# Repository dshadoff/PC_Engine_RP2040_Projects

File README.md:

# PC_Engine_RP2040_Projects - Projects designed for PC Engine, using RPi Pico or other RP2040 hardware

## [Memory Base 128 reimplementation](https://github.com/dshadoff/PC_Engine_RP2040_Projects/tree/main/Membase)

This is the third implementation of the Memory Base 128 I have written for modern hardware, and the easiest code to read.
The PIOs areused for edge-sensing of the data input, and the ARM core is used for processing.

The data is loaded into SRAM at startup, and saved into Flash after transactions take place.  This may not be ideal, as the
device is not capable of processing additional commands while the Flash flush is in progress (it takes place 0.75 seconds
after the last read/write of a group of read or write transactions).

## [PC Engine USB Mouse adapter](https://github.com/dshadoff/PC_Engine_RP2040_Projects/tree/main/PCEMouse)

This allows a modern USB mouse to be used by a PC Engine machine.  The PC Engine did have a mouse later in the console's
lifetime; it was a mouse with a rotating ball and a cord (anybody familiar with this type of mouse would be familiar
with the desire to use a modern cordless optical mouse).

The RP2040 board is used as the USB Host for the mouse, and PIOs are used for signalling to the PC Engine console.

## Others

Other Projects are coming... the PIOs on the RPi Pico are very interesting and flexible, so will be well-suited to
retrocomputing/retrogaming projects.

## Notes
I initially used the Adafruit QtPy RP2040 as much as possible, as it is a compact form factor which is easy to design around; however,
I have also warmed up to the Seeed XIAO for having the same form factor, but with no parts on the underside (making soldering on the
castellations easier), and lower price.  The Adafruit KB2040 is also very attractive because it breaks out the USB pins so that alternate
USB connectors can be used (such as USB-A connectors for mouse devices).

Unfortunately, for the QtPy 2040, the Adafruit site tries to direct all users toward CircuitPython rather than C/C++ (the Pi SDK), and
as a result, Pinout pages of the "Pinout" page for their RP2040 devices don't include references to the GPIO numbers.

Therefore, I am including a graphic here:

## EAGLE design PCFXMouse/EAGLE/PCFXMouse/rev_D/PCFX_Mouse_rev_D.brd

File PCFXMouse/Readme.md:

# PC_Engine_RP2040_Projects - PC-FX Mouse converter

## Overview

This project is intended to allow use of a standard USB mouse on a PC-FX.
I have revised this project a few times, and arrived at using an Adafruit KB2040 microcontroller board, as it uses the
excellent RP2040 microcontroller, and due to its breakout of the USB lines, which allows for an external USB-A connector.

## PC Board and Assembly

I designed all boards using the free version of EAGLE (2-layer, less than 100mm on both X- and Y- axes).
The gerbers are included in this repository, in case you want to get your own set made.

I have included the gerbers and relevant bom.csv and assembly.csv files to get these boards
assembled by JLCPCB, but you will still need the following parts:
- (1) Adafruit KB2040 RP2040 microcontroller board
- (7) pieces of Mill-Max pin&socket connector, Part number 4401-0-15-80-18-27-04-0

Optional:
- (2) 13-pin headers.  You may also want to use female pin header sockets in case you need to remove the microcontroller board.
I recommend using short/low-profile header sockets in this case.

There are two PC Boards in this assembly; one functions as part of the host connector.
For that PC Board, you will need the Mill-Max pin&socket connectors.

The way I assembled it was to carefully put the pin connectors on their respective pins, then
position the PC board over top, and solder in place.

Steps to assembly:

See the Assembly Guide
**[See the Assembly Guide](Assembly.md)**

## Source Code

### Compilation

This code is now updated to Pico-SDK version 1.5.0, and should be built using that version of the SDK.
pico_sdk_import.cmake is from the SDK, but is required by CMake (and thus replicated here).

This is based on the TinyUSB Host HID example, and since this often changes (required by refactoring of
the Host HID code), the initial commit baseline is the source ocde of that example.

To build the source, first ensure that you have the right version of the RaspberryPi/piso-sdk installed.
As this board targets the Adafruit KB2040 board, you should run the build_kb2040.sh script (under UNIX).
Then, "cd build" and "make".

I have also included a release version of the program as a uf2 file in the releases/ folder; just drag and drop it
onto the virtual drive presented when putting the board into BOOTSEL mode (holding the 'boot' button, connect the
board by USB to a host computer, and release the button; a new drive should appear on the computer).

### Theory of Operation

At a high level, this is a multi-processor system, withe the division of work as follows:
- CPU0 : perform USB scanning, accumulate X/Y offsets and button status, and push a word conatining all this to PIO State Machine #1.
At intervals, detect whether the scan interval must be complete (after a certain threshold period).
- CPU1 : watch PIO State Machine #1 for the signal identifying start of scan; set locking to prevent mid-scan updates
- PIO State Machine #1 : Monitor host electrical signals, and send the appropriate bit(s) back to host according to protocol
- PIO State Machine #2 : Watch the trigger line identifying the start of scan, and send the signal back to CPU1

#### PC-FX Mouse/Controller Protocol:

Similar to the NES or SNES, the PC-FX Engine triggers a start-of-read trigger by bringing the LATCH line
low.  The first bit of data is output at this time. After the LATCH signal returns to the high state, each
subsequent bit is sent at the transition of the CLOCK signal to high.

In the below diagram, LATCH is the top trace, CLOCK is the middle trace, and DATA sent back is the bottom trace
(/OE defines the data direction - LOW=Read controller; HIGH=Write to controller:\

The first bit sent is the least significant, and the most significant bit is sent last.  The last byte in
the sequence is a controller type identifier - 0x2F = Mouse, and 0x0F = Joypad.

The below data diagram shows how the data is internally passed to the state machien for output:

    Structure of the word sent to the FIFO from the ARM:
    |00101111|111111bb|xxxxxxxx|yyyyyyyy| (PCFX mouse)
    |00001111|11111111|1m1mdddd|rsbbbbbb| (PCFX joypad)
    
     Where:
      0 = must be zero
      1 = must be one
     MOUSE:
      b = button values, arranged in right/left sequence for PC-FX use
      x = mouse 'x' movement; right is {1 - 0x7F} ; left is {0xFF - 0x80 } -> but send as 1's complement !
      y = mouse 'y' movement; down  is {1 - 0x7F} ;  up  is {0xFF - 0x80 } -> but send as 1's complement !
    
     NOTES:
      - PC-FX left/right is (-/+) (but sent as complement - i.e. sned 0xFF if value is zero)
      - PC-FX up/down is (-/+) (but sent as complement - i.e. sned 0xFF if value is zero)

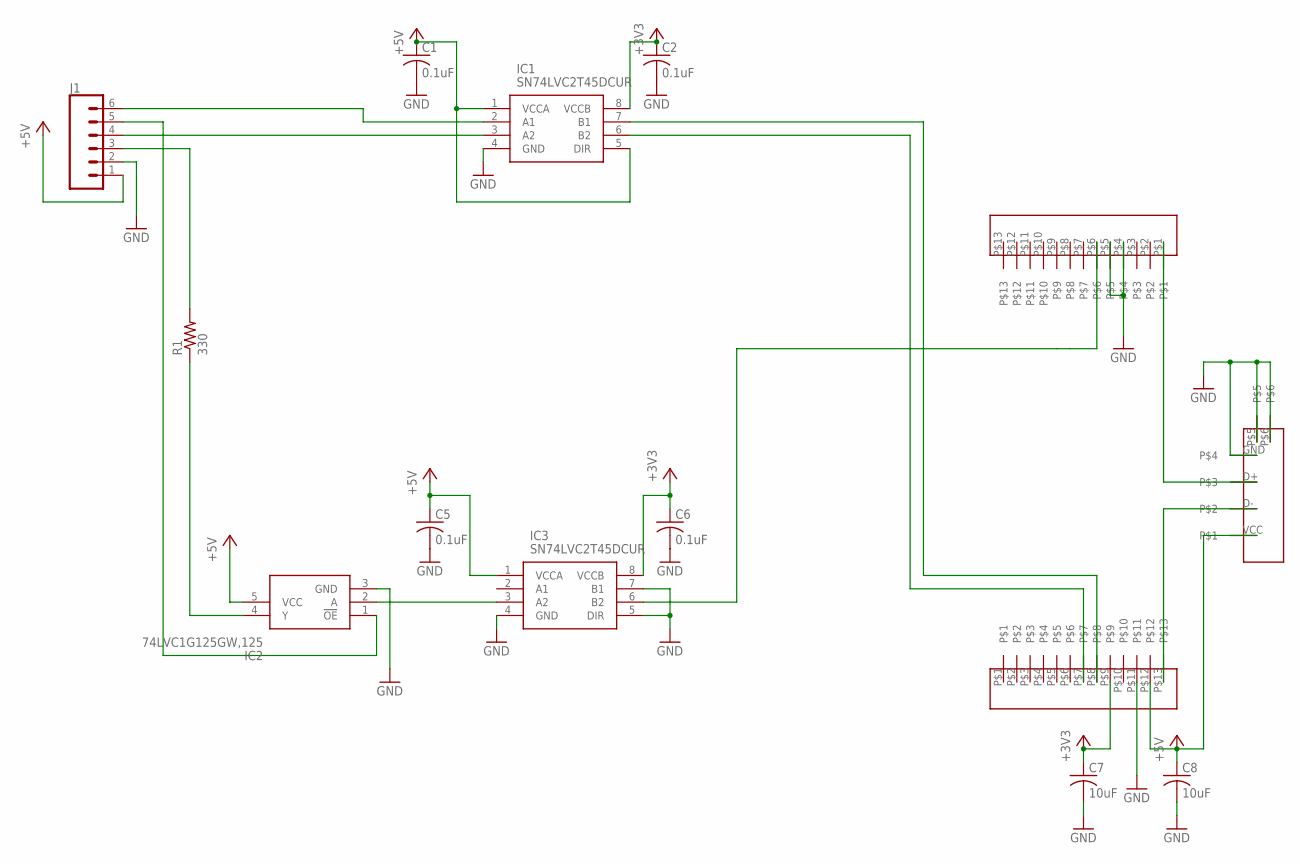
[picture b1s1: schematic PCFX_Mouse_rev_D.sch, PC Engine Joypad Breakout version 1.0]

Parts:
C1, C2, C5, C6: 0.1uF; C0402
C7, C8: 10uF; C0805
IC1, IC3: SN74LVC2T45DCUR; SOP50P310X90-8N
IC2: 74LVC1G125GW,125; SOT65P212X110-5N
J1: CONN_06NO_SILK_FEMALE_PTH; 1X06_NO_SILK
J2, J3: CONN_1X13
R1: 330; R0402
U$1: 912-121A2026S10100

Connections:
+3V3: C2.1, C6.1, C7.1, IC1.8 (VCCB), IC3.8 (VCCB), J2.P$9
+5V: C1.1, C5.1, C8.1, IC1.1 (VCCA), IC1.5 (DIR), IC2.5 (VCC), IC3.1 (VCCA), J1.1, J2.P$12, U$1.VCC
CLK: IC1.3 (A2), J1.4
DATA: J1.3, R1.2
GND: C1.2, C2.2, C5.2, C6.2, C7.2, C8.2, IC1.4 (GND), IC2.3 (GND), IC3.4 (GND), IC3.5 (DIR), IC3.7 (B1), J1.2, J2.P$11, J3.P$4, J3.P$5, U$1.GND, U$1.P$5, U$1.P$6
LATCH: IC1.2 (A1), J1.6
unnamed: IC2.2 (A), IC3.3 (A2)
unnamed: IC1.7 (B1), J2.P$8
unnamed: IC3.6 (B2), J3.P$6
unnamed: J2.P$13, U$1.D-
unnamed: IC2.1 (!OE), J1.5
unnamed: J3.P$1, U$1.D+
unnamed: IC1.6 (B2), J2.P$7
unnamed: IC2.4 (Y), R1.1

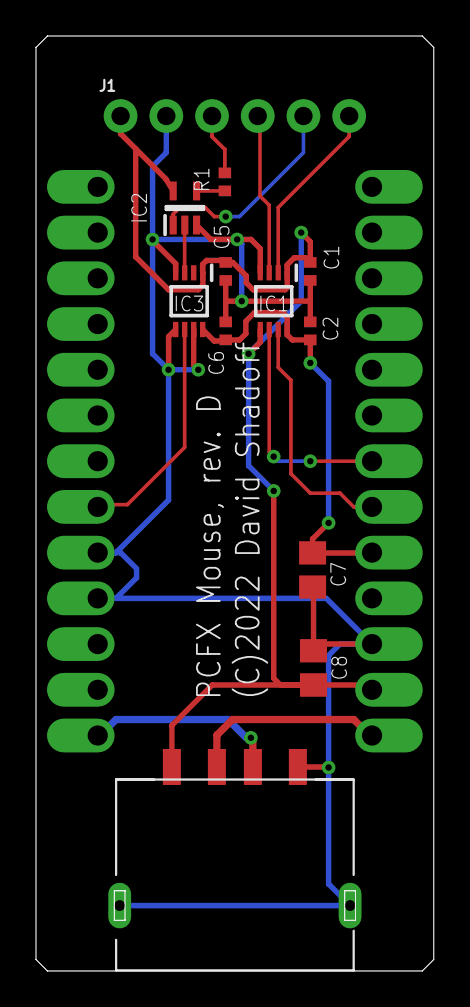
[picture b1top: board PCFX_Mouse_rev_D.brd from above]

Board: 2 copper layers, 22.1 x 51.9 mm, 14 parts (0 on the bottom side), 14 nets.

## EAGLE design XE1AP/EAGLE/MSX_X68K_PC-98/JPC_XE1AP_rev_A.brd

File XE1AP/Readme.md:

# PC_Engine_RP2040_Projects - XE-1AP Analog Joystick Converter

## Overview

This project is intended to allow use of a standard USB-based PS4 gamepad on a PC Engine as a XE-1AP analog joypad.
While the code and board are in working condition, there is likely still room for improvement, as I feel that
analog positioning may not be as smooth as it could be.

## PC Board and Assembly

This project has several different possible "carrier" boards, depending on which host machine you are targeting.
All are deigned in EAGLE; all include schematic, board layout, and gerber files.  They also include BOM and assembly files
for JLCPCB SMD assembly.

### PC Engine

This is the same PC Board used in the "PCEMouse" project in this repository (KB2040 board version), however I have copied
the contents here for simplicity for users.

### Japanese PCs (MSX, X68000, PC-98, etc.)

This is a slightly differnet carrier board with a DB-9 connector, for Japanese MSX, X68000, and PC-98 machines.  It uses the SAME
KB2040 and the SAME firmware as the PC Engine version.

Next, I intend to make a board to work with the Megadrive.

## Source Code

### Compilation

This was updated to use Pico-SDK version 1.5.0 .

pico_sdk_import.cmake is from the SDK, but is required by CMake (and thus replicated here)

This is based on the TinyUSB Host HID controller example, and since this often changes (required by refactoring of
the Host HID code), the initial commit baseline is the source code of that example.

To build the source, first ensure that you have the right version of the RaspberryPi/piso-sdk installed.
As this board targets the Adafruit KB2040 board, you should run the build_ada_kb2040.sh script (under UNIX).
Then, "cd build" and "make".

I have also included a release version of the program as a uf2 file in the releases/ folder; just drag and drop it
onto the virtual drive presented when putting the board into BOOTSEL mode (holding the 'boot' button, connect the
board by USB to a host computer, and release the button; a new drive should appear on the computer).

### Theory of Operation

At a high level, this is a multi-processor system, withe the division of work as follows:
- CPU0 : perform USB scanning, analyze controller button statuses and joysticks' X/Y offsets, and keep the data up-to-date in a temporary storage area.
- CPU1 : watch PIO State Machine #1 for the signal identifying start of scan, set locking to prevent mid-scan updates, and push the series of last-known-good data to state machine #2.
- PIO State Machine #1 : Monitor host electrical signals, blocking thread #1 until triggereed, and signalling state machine #2 to start its
protocol via an IRQ signal.
- PIO State Machine #2 : Wait for IRQ signal from state machine #1, and then send the data out on the GPIOs according to the standard timing (get the data from the TX FIFO as sent by CPU1).
- PIO State Machine #3 : Watch the SEL line identifying which bits to multiplex, and send the correct bits out through the data outputs
(note: the XE3-HE did not multiplex these in the same sequence as the Megadrive, so some bit-rearranging takes place here).

#### XE-1AP Protocol:

The PC Engine triggers a start-of-read trigger by flipping the CLR line low briefly, and returning it to HIGH.  Note that this is
not normal behaviour, and the XE-1AP is NOT compatible with the multi-tap. Immediately following the rise of the CLR line, the
joystick values are latched. During this time, SEL is held LOW as the PC Engine is expected to watch for state transitions on the
buttons 'I' and 'II', which are on D0 and D1 respectively.  D0 is LOW and D1 is HIGH during the waiting period.
After roughly 68.4 microseconds, data is ready, which is signalled by D1 (button 'II') transitioning low.

When the console sees this, its duty is to transition SEL to HIGH, in order to read the four data bits on D0-D3
(which normally correspond to UP/DOWN/LEFT/RIGHT), which in this situation correspond to the first nybble of data
from the joystick.  Then, SEL needs to transition back to LOW in order to monitor D0 and D1 again.  The window of data
availability (when button 'II' stays LOW) is fairly short, roughly 12.1 microseconds, requiring a tight loop on the
host console.

Before the next nybble is made available, button 'II' transitions HIGH for roughly 3.8 microseconds while data lines
transition.  Button 'I' transitions HIGH, representing the second nybble - and button 'II' transitions LOW again (for
12.1 microseconds again), signalling data ready, and the console needs to fetch the nybble by toggling SEL and reading
the lines during the availability window.

When button 'II' toggles high again, this time it stays high for longer (to prepare for the next 2 nybbles), at
21.8 microseconds.  The pattern repeats, with 6 bytes (12 nybbles) in all being transferred; the entire time from the
initial pulse to the end of the data transfer is roughly 350 microseconds.

Note that timing on this implementation is rounded to the next higher number of microseconds in most situations, with the difference
being removed from the 'dead' times between the second half of one byte, and the first half of the next byte being sent.

#### Data sequence output:

The sequence of data (and bit-order) is as follows (from original joystick):

All values are low when pressed, high when not pressed

 1. Buttons A, B, C, D - (Note: A is pressed if either A or A' is pressed; same with B or B')
 2. Buttons E1, E2, Start(F), Select (G)
 3. Top 4 bits of 'channel 0' (Y-axis;   limit up   = 0x00, limit down  = 0xFF)
 4. Top 4 bits of 'channel 1' (X-axis;   limit left = 0x00, limit right = 0xFF)
 5. Top 4 bits of 'channel 2' (Throttle; limit up   = 0xFF, limit down  = 0x00)
 6. 0000 (unused)
 7. Bottom 4 bits of 'channel 0' (Y-axis)
 8. Bottom 4 bits of 'channel 1' (X-axis)
 9. Bottom 4 bits of 'channel 2' (Throttle)
10. 0000 (unused)
11. Buttons A, B, A', B' (This can differentiate between the buttons, whereas scan #1 merges them)
12. 1111 (all high)

#### Logic state diagram:

**Compatibility:** Games which are not specifically written to support the X-HE3/XE-1AP in analog format will not work properly with this code.

Compatible games include:
 - AfterBurner II
 - Forgotten Worlds
 - Operation Wolf
 - Outrun

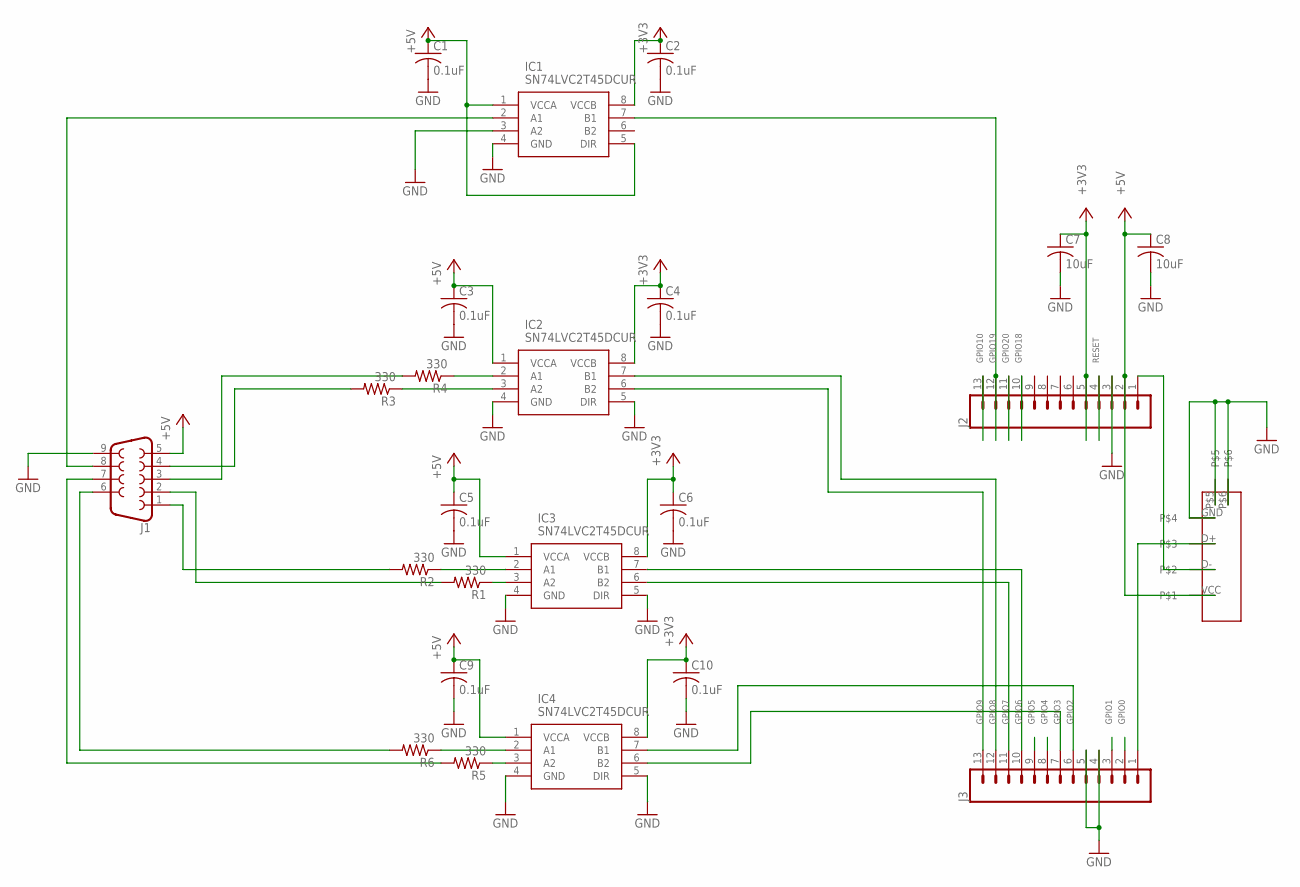
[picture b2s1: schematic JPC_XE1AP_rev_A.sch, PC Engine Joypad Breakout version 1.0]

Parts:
C1, C2, C3, C4, C5, C6, C9, C10: 0.1uF; C0402
C7, C8: 10uF; C0805
IC1, IC2, IC3, IC4: SN74LVC2T45DCUR; SOP50P310X90-8N
J1: DB9FEMALE; DB9
J2: CONN_131X13-LONGPADS-B; 1X13-LONGPADS-B
J3: CONN_13LONGPADS; 1X13-LONGPADS
R1, R2, R3, R4, R5, R6: 330; R0402
U$1: 912-121A2026S10100

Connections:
+3V3: C2.1, C4.1, C6.1, C7.1, C10.1, IC1.8 (VCCB), IC2.8 (VCCB), IC3.8 (VCCB), IC4.8 (VCCB), J2.5
+5V: C1.1, C3.1, C5.1, C8.1, C9.1, IC1.1 (VCCA), IC1.5 (DIR), IC2.1 (VCCA), IC3.1 (VCCA), IC4.1 (VCCA), J1.5, J2.2, U$1.VCC
CLR: IC1.2 (A1), J1.8
GND: C1.2, C2.2, C3.2, C4.2, C5.2, C6.2, C7.2, C8.2, C9.2, C10.2, IC1.3 (A2), IC1.4 (GND), IC2.4 (GND), IC2.5 (DIR), IC3.4 (GND), IC3.5 (DIR), IC4.4 (GND), IC4.5 (DIR), J1.9, J2.3, J3.4, J3.5, U$1.GND, U$1.P$5, U$1.P$6
GPIO0: J3.2
GPIO1: J3.3
GPIO2: IC4.7 (B1), J3.6
GPIO3: IC4.6 (B2), J3.7
GPIO4: J3.8
GPIO5: J3.9
GPIO6: IC3.7 (B1), J3.10
GPIO7: IC3.6 (B2), J3.11
GPIO8: IC2.7 (B1), J3.12
GPIO9: IC2.6 (B2), J3.13
GPIO10: J2.13
GPIO18: J2.10
GPIO19: IC1.7 (B1), J2.12
GPIO20: J2.11
unnamed: J3.1, U$1.D+
unnamed: J1.1, R2.2
unnamed: IC4.2 (A1), R6.1
unnamed: IC4.3 (A2), R5.1
unnamed: J1.2, R1.2
unnamed: J1.3, R4.2
unnamed: J1.4, R3.2
unnamed: IC3.3 (A2), R1.1
unnamed: IC3.2 (A1), R2.1
unnamed: IC2.3 (A2), R3.1
unnamed: IC2.2 (A1), R4.1
unnamed: J2.1, U$1.D-
unnamed: J1.6, R6.2
unnamed: J1.7, R5.2
RESET: J2.4

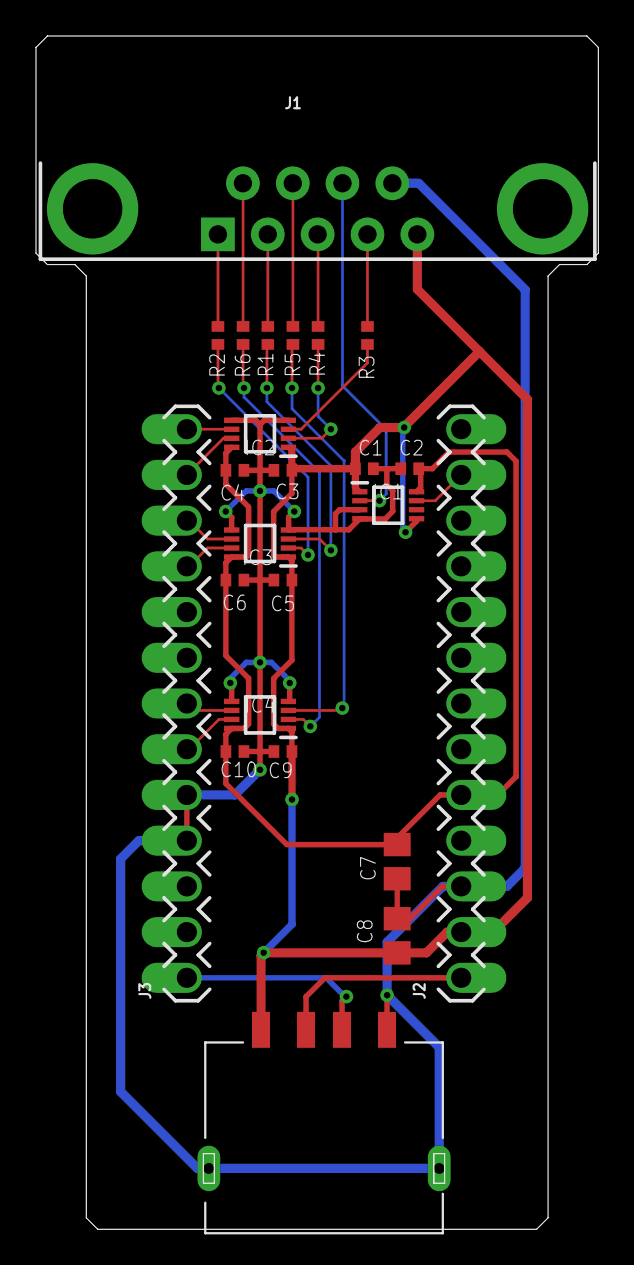
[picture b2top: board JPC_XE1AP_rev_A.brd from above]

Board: 2 copper layers, 31.2 x 66.3 mm, 24 parts (0 on the bottom side), 25 nets.

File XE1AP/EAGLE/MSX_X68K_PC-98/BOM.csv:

Qty,Designator,Footprint,Comment,LCSC Part # (optional),Description (optional)
1,J2,1X13-LONGPADS-B,Do not mount,Do not mount,Multi connection point. Often used as Generic Header-pin footprint for 0.1 inch spaced/style header connections
1,J3,1X13-LONGPADS,Do not mount,Do not mount,Multi connection point. Often used as Generic Header-pin footprint for 0.1 inch spaced/style header connections
1,J1,DB9,Do not mount,Do not mount,DB9 Connector
8,"C1, C2, C3, C4, C5, C6, C9, C10",C0402,100nF 16V,C1525,Samsung CL05B104KO5NNNC 100nF 16V 0402
2,"C7, C8",C0805,10uF 25V,C15850,Samsung CL21A106KAYNNNE  10uF 25V 0805
6,"R1, R2, R3, R4, R5, R6",R0402,330R,C25104,Uniroyal Elec  0402WGF3300TCE  0402
1,U$1,USB-A-TH,912-121A2026S10100,C42425,USB 2.0 1 4 Female Type-A SMD USB Connectors ROHS
4,"IC1, IC2, IC3, IC4",VSSOP-8_2.0x2.3x0.5P,SN74LVC2T45DCUR,C15741,"2-Bit Bus Transceiver, Translation VSSOP-8_2x2.3x05P SN74LVC2T45DCTR, Voltage Level Translator, Bus Transceiver LVC, 3-State 1.65"

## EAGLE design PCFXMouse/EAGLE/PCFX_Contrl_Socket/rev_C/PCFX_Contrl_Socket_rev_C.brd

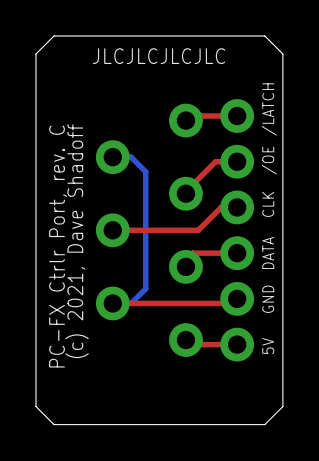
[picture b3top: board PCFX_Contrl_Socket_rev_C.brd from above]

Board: 2 copper layers, 13.7 x 21.6 mm, 8 parts (0 on the bottom side), 6 nets.

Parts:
J1, J2, J3, J4, J5, J6, J7: 1X01_NO_SILK
J9: 1X06_NO_SILK

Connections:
GND: J5.1, J7.1, J9.5
unnamed: J4.1, J9.1
unnamed: J3.1, J9.2
unnamed: J6.1, J9.3
unnamed: J2.1, J9.4
unnamed: J1.1, J9.6

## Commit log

2022-07-10 Add sensitivity adjustment, using scroll wheel
    This can be enabled/disabled by commenting/uncommenting the definition of the preprocessor variable 'SENSITIVITY_SCROLL' in 'hid_app.c'.
    I felt it worked well without being too distracting, so I've left it enabled.
2022-09-24 Add new XE1AP project (for PCEMouse board)
2022-09-24 Rename with date
2022-10-02 Update values on every report; include code to track frequency of reports (4ms was found)
2022-10-03 Add carrier boards for XE1-AP for different machines
2022-10-09 Update for FX-Mouse to support Seeed XIAO RP2040
2022-10-31 Correct filename
2022-11-01 Update FXMouse to KB2040 version
2022-11-01 Update assembly instructions
2022-11-06 Add selectable sensitivity to mouse
2023-03-13 Updated PCEMouse, PCFXMouse, and XE1AP to SDK 1.5.0
2023-07-18 Move PC-FX project to separate repo

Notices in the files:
PCFXMouse/EAGLE/PCFXMouse/rev_D/PCFX_Mouse_rev_D.brd:
(C)2022 David Shadoff
PCFXMouse/EAGLE/PCFX_Contrl_Socket/rev_C/PCFX_Contrl_Socket_rev_C.brd:
(c) 2021, Dave Shadoff
parts and their libraries:
SparkFun-Connectors: Licensing: Creative Commons ShareAlike 4.0 International - https://creativecommons.org/licenses/by-sa/4.0
